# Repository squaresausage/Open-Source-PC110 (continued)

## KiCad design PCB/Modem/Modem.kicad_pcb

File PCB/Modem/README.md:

## Here is the PCB Layout for the Modem Board

Layer Stack-up

| Index | Layer name | Description  |
| ----- | ---------- | ------------ |
| 1     | FC         | Top          |
| 2     | IC1        | Signal       |
| 4     | IP1        | Power        |
| 3     | IP2        | Power        |
| 4     | IC2        | Signal       |
| 4     | BC         | Bottom       |

Here is a render of FC, IC1, IP1, IP2, IC2 and BC:

Here are the 3D renders from the board:

PCB statistics report
=====================
- Date: Friday, March 21, 2025 at 08:35:15 PM
- Project: Modem
- Board name: Modem

Board
-----
- Width: 64.6100 mm
- Height: 58.9100 mm
- Area: 3494.8376 mm²

Pads
----
- Through hole: 23
- SMD: 735
- Connector: 0
- NPTH: 0

Vias
----
- Through vias: 344
- Blind/buried: 0
- Micro vias: 0

Components
----------

|              | Front Side | Back Side | Total |
|--------------|------------|-----------|-------|
|THT:          |          0 |         0 |     0 |
|SMD:          |         75 |       136 |   211 |
|Unspecified:  |          0 |         0 |     0 |
|Total:        |         75 |       136 |   211 |

Drill holes
-----------

| Count | Shape |    X Size |    Y Size | Plated | Via/Pad | Start Layer | Stop Layer |
|-------|-------|-----------|-----------|--------|---------|-------------|------------|
|   344 | Round | 0.3000 mm | 0.3000 mm |    PTH |     Via |          FC |         BC |
|    18 | Round | 1.0000 mm | 1.0000 mm |    PTH |     Pad |          FC |         BC |
|     5 | Round | 1.2000 mm | 1.2000 mm |    PTH |     Pad |          FC |         BC |

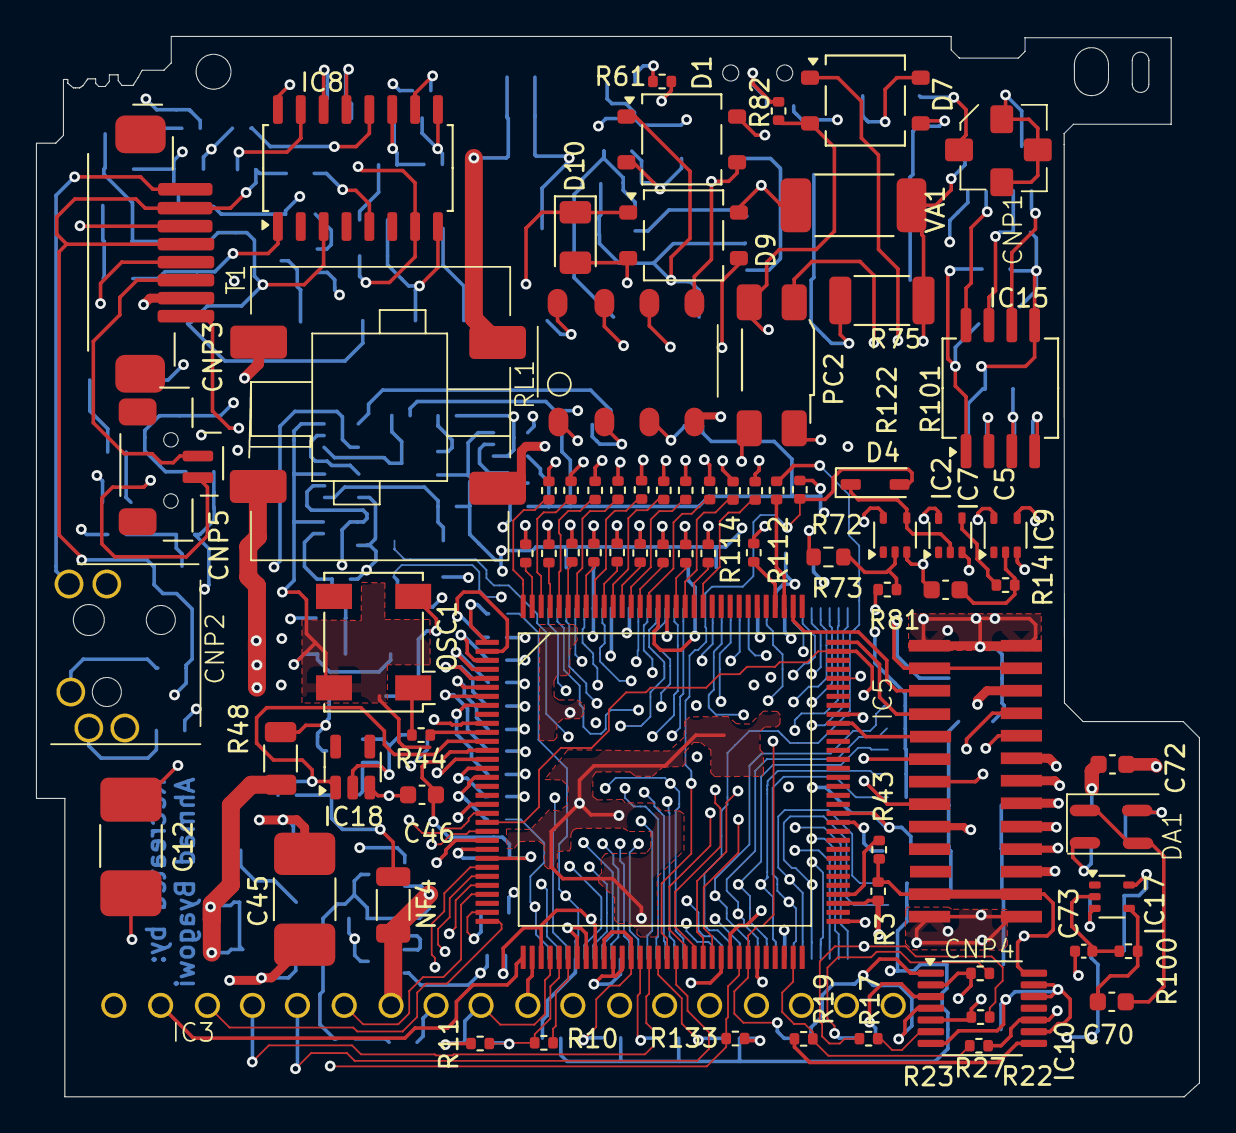
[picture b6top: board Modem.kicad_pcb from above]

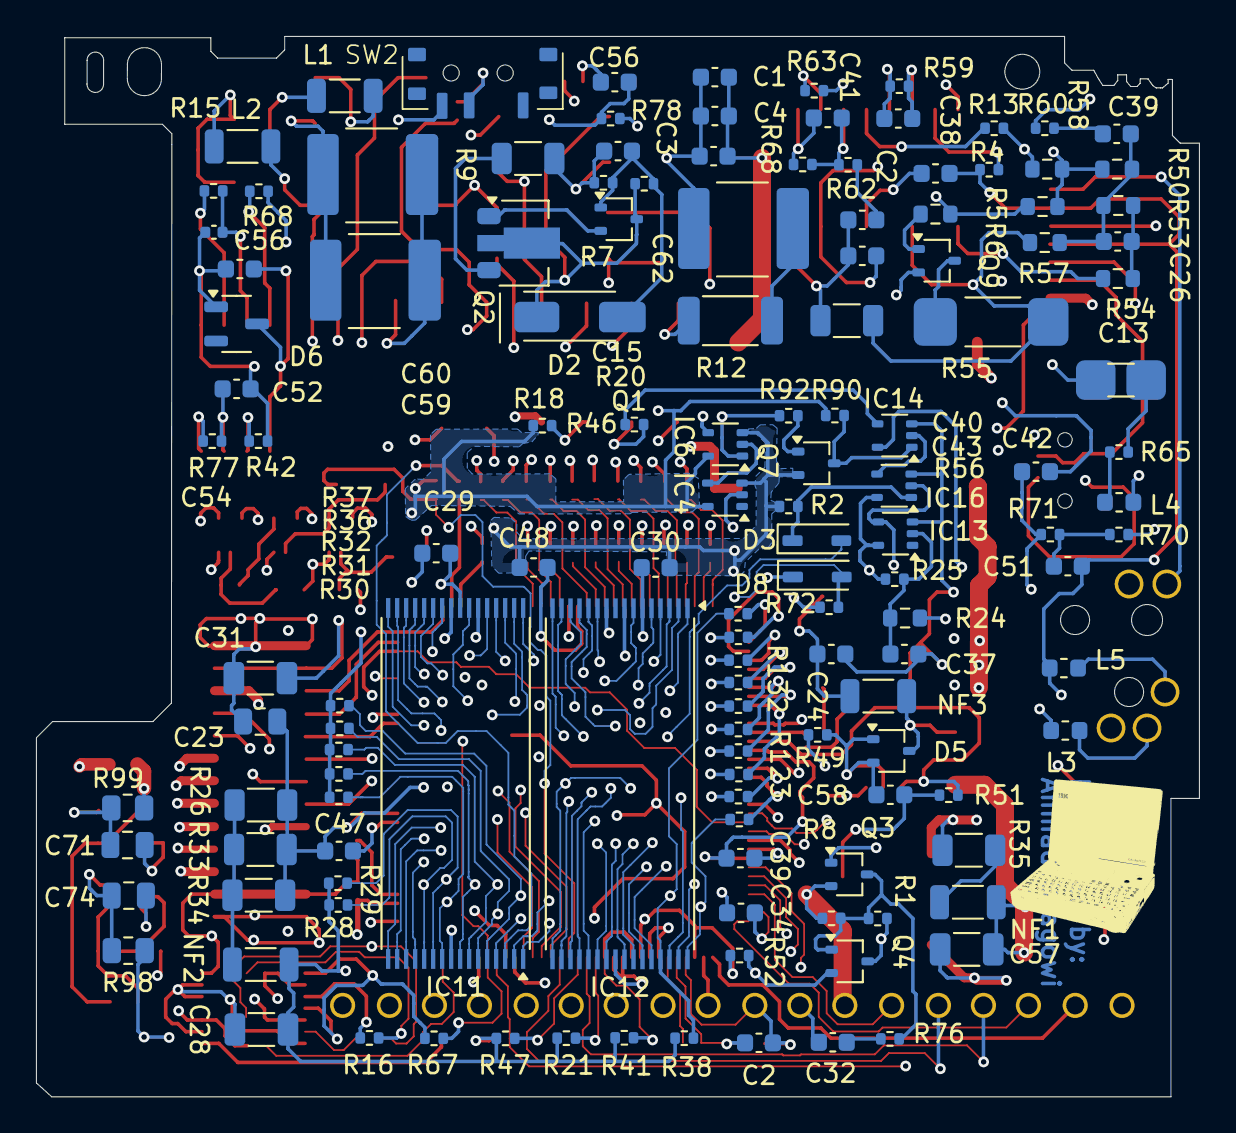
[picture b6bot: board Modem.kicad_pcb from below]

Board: 6 copper layers, 64.6 x 58.9 mm, 211 parts (136 on the bottom side), 205 nets.

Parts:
C1, C4, C52, C54: 330nF; C_0603_1608Metric
C2, C34: 1nF; C_0603_1608Metric
C2#2, C15, C32: 1.2uF; C_0603_1608Metric
C3: 30nF; C_0603_1608Metric
C5: 250nF; C_0603_1608Metric
C12, C45: 47uF 16v; C_1812_4532Metric
C13: 822J; C_1206_3216Metric
C23: 1.2uF; C_0805_2012Metric
C24, C37: 230nF; C_0603_1608Metric
C26: 10nF; C_0603_1608Metric
C28: 8.1uF; C_1206_3216Metric
C29, C30: 1.5uF; C_0603_1608Metric
C31: 230nF; C_1206_3216Metric
C38: 2.2uF; C_0603_1608Metric
C39: 100nF; C_0603_1608Metric
C39#2, C48: 25nF; C_0603_1608Metric
C40: 16nF; C_0603_1608Metric
C41, C43: 1uF; C_0603_1608Metric
C42, C51: 1.2nF; C_0603_1608Metric
C46, C47: 24nF; C_0603_1608Metric
C56: 1.6nF; C_0402_1005Metric
C56#2: 470nF; C_0603_1608Metric
C57: 6.8uF; C_1206_3216Metric
C58: 220nF; C_0603_1608Metric
C59, C60, C62: 280nF; C_2220_5750Metric
C70, C72: 1.8uF; C_0603_1608Metric
C71: 1.3uF; C_0805_2012Metric
C73: 100pF; C_0402_1005Metric
C74: 220nF; C_0805_2012Metric
CNP1: Line_Connector
CNP2: modem_heaset_jack
CNP3: JST_8_headset_connector
CNP4: Modem-Connector
CNP5: JST_2_modem_spkr
D1, D7, D9: TO-269AA
D2: 1N4148; D_SOD-128
D3, D4, D8: 5; D_1206_3216Metric_modem
D5: 3D; SOT-323_SC-70
D6: 30H; SOT-23-3
D10: 152; D_1206_3216Metric
DA1: M1T; DA_Modem
IC2, IC7, IC9, IC13, IC17: EA; SOT-353_SC-70-5
IC3: Line-Module
IC4: E5; SOT-353_SC-70-5
IC5: MN195
IC6: 54; SOT-353_SC-70-5
IC8: TA31033F; SOIC-16_4.55x10.3mm_P1.27mm
IC10: AT32 433; TSSOP-14_4.4x5mm_P0.65mm
IC11: EN29F040A; TSOP-I-32_18.4x8mm_P0.5mm_Reverse
IC12: KM681000BLT-7 (I-Reverse); TSOP-I-32_18.4x8mm_P0.5mm_Reverse
IC14: E4; SOT-353_SC-70-5
IC15: 8206 5877; SOIC-8_5.3x6.2mm_P1.27mm
IC16: E3; SOT-353_SC-70-5
IC18: 3L01; TSOT-23-5
L1, L2: 1.2uH; L_1206_3216Metric
L3, L5: 1.8uH; L_0603_1608Metric
L4: 1.2uH; L_0603_1608Metric
NF1: 300nH; L_1206_3216Metric
NF2, NF4: 4.7nH; L_1206_3216Metric
NF3: 0; L_1206_3216Metric
OSC1: 41.472; Oscillator_SMD_Fordahl_DFAS2-4Pin_7.3x5.1mm
PC2: TLP124; Everlight_ITR8307_Reverse
Q1, Q4: CQ; SOT-323_SC-70
Q2: DA QU; SOT-89-3
Q3: 123; SOT-323_SC-70
Q7: SOT-323_SC-70
Q9: HP; SOT-323_SC-70
R1: 12k; R_0402_1005Metric
R2, R3, R28, R29, R30, R31, R32, R36, R37, R38, R41, R43: 4.7k; R_0402_1005Metric
R4: 330; R_0402_1005Metric
R5: 100; R_0603_1608Metric
R6: 3.3k; R_0603_1608Metric
R7, R26, R33, R34: 10; R_1206_3216Metric
R8: 22k; R_0402_1005Metric
R9, R20, R63, R81: 100k; R_0402_1005Metric
R10, R11, R68: 38k; R_0402_1005Metric
R12, R75: 2.2k; R_2010_5025Metric
R13, R16, R17, R19, R21, R47, R49, R62, R67, R82, R133: 10k; R_0402_1005Metric
R14: 560k; R_0402_1005Metric
R15: 330k; R_0402_1005Metric
R18, R46: 1.5k; R_0402_1005Metric
R22, R23, R27: DNP; R_0402_1005Metric
R24: 200; R_0603_1608Metric
R25: 500k; R_0402_1005Metric
R35: 20; R_1206_3216Metric
R42: 15k; R_0402_1005Metric
R44: 51; R_0402_1005Metric
R48: 3.3; R_1206_3216Metric
R50: 6.2k; R_0603_1608Metric
R51, R72, R72#2, R90, R100: 470k; R_0402_1005Metric
R52, R70, R71: 1k; R_0402_1005Metric
R53: 11k; R_0603_1608Metric
R54: 1.5k; R_0603_1608Metric
R55: 82; R_2010_5025Metric
R56: 15; R_1206_3216Metric
R57: 150; R_0603_1608Metric
R58: 620; R_0603_1608Metric
R59, R60: 2.2k; R_0402_1005Metric
R61: 3.6k; R_0402_1005Metric
R65: 15; R_0402_1005Metric
R68#2: 20k; R_0402_1005Metric
R73: 120; R_0603_1608Metric
R76: 2.4k; R_0402_1005Metric
R77: 270k; R_0402_1005Metric
R78: 5.6k; R_0402_1005Metric
R92: 47k; R_0402_1005Metric
R98, R99: 100; R_0805_2012Metric
R101, R102, R103, R104, R105, R106, R107, R108, R109, R110, R111, R112, R114, R115, R116, R117, R118, R119, R120, R121, R122, R123, R124, R124#2, R125, R126, R127, R129, R130, R131, R132: 100; R_0402_1005Metric
RL1: RL
SW2: SW_modem
T1: IsoTransformer
VA1: R_2512_6332Metric

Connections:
29FA7: IC11.20, IC12.13, R119.1
29F_A0: IC11.13, IC12.20, R111.1
29F_A1: IC11.14, IC12.19, R122.1
29F_A2: IC11.15, IC12.18, R110.1
29F_A3: IC11.16, IC12.17, R121.1
29F_A4: IC11.17, IC12.16, R109.1
29F_A5: IC11.18, IC12.15, R120.1
29F_A6: IC11.19, IC12.14, R108.1
29F_A8: IC11.30, IC12.3, R107.1
29F_A9: IC11.31, IC12.2, R118.1
29F_A10: IC11.2, IC12.31, R106.1
29F_A11: IC11.32, IC12.1, R117.1
29F_A12: IC11.21, IC12.12, R105.1
29F_A13: IC11.29, IC12.4, R116.1
29F_A14: IC11.28, IC12.11, R104.1
29F_A15: IC11.22, IC12.7, R115.1
29F_A16: IC11.23, IC12.10, R103.1
29F_A17: IC11.27, R114.1
29F_A18: IC11.24, R102.1
29F_CE#: IC11.3, R101.1
29F_DQ0: IC11.12, IC12.21, R28.2, R125.1
29F_DQ1: IC11.11, IC12.22, R29.2, R126.1
29F_DQ2: IC11.10, IC12.23, R30.2, R127.1
29F_DQ3: IC11.8, IC12.25, R31.2, R124#2.1
29F_DQ4: IC11.7, IC12.26, R32.2, R129.1
29F_DQ5: IC11.6, IC12.27, R36.2, R130.1
29F_DQ6: IC11.5, IC12.28, R37.2, R131.1
29F_DQ7: IC11.4, IC12.29, R38.2, R132.1
29F_OE#: IC11.1, IC12.32, R123.1
29F_WE#: IC11.26, IC12.5, R124.1
C32_1: C32.1, IC3.8
C32_2: C32.2, R76.1
C39_1: C39.1, R60.2
C40_2: C40.2, R62.2
C51_1: C51.1, R70.1, R71.2
C52_2: C52.2, C54.1, C56.1, D6.1, D7.2, IC15.5, PC2.3, R42.2, R82.1
C70_1: C70.1, IC17.4, R100.1
C70_2: C70.2, DA1.1, DA1.4
C72_1: C72.1, IC3.12, R99.2
C74_1: C74.1, IC17.5, R98.1
CNP2_2: CNP2.2, CNP3.3
CNP2_3: CNP2.3, L4.2
CNP3_1: CNP2.4, CNP3.1
CNP3_5: CNP3.5, R78.2
CNP5_1: CNP5.1, SW2.3
CNP5_2: CNP3.6, CNP5.2
D1_1: D1.1, D2.1, Q1.3, Q2.2, R20.1
D1_2: C15.1, D1.2, R7.2, R9.1
D2_2: C15.2, D2.2, Q1.1, R9.2, R20.2
D4_1: D4.1, IC2.4, IC7.2
D7_1: C54.2, D6.3, D7.1, IC15.1
D7_3: C59.1, C60.1, D7.3
DA1_2: C71.1, DA1.2, R99.1
FDC_CTS1#: CNP4.8, IC10.5, R23.2
FDC_DCD1_PC110: CNP4.4, IC5.65
FDC_DIR1#_PC110: CNP4.6, IC5.54
FDC_DSR1_PC110: CNP4.7, IC5.51
FDC_RI1_PC110: CNP4.5, IC10.2, R22.2
FDC_RTS1#_PC110: CNP4.9, IC5.53
FDC_RXD1_PC110: CNP4.10, IC5.52
FDC_TXD1_PC110: CNP4.11, IC9.4
GND: C5.1, C23.1, C24.2, C28.1, C29.1, C30.2, C31.1, C37.2, C39#2.2, C46.1, C47.2, C48.1, C58.2, CNP3.8, CNP4.1, CNP4.13, CNP4.14, CNP4.26, IC2.3, IC4.3, IC5.10, IC5.14, IC5.19, IC5.24, IC5.43, IC5.44, IC5.76, IC5.112, IC6.3, IC7.3, IC9.3, IC10.1, IC10.4, IC10.7, IC10.9, IC10.12, IC10.13, IC11.9, IC12.24, IC13.3, IC14.3, IC16.3, IC18.3, NF4.2, OSC1.4, Q7.2, R2.1, R51.1, R67.1, R81.1
IC3_15: IC3.15, T1.3
IC6_2: IC4.4, IC6.2
IC7_4: IC7.4, R14.1
IC8_3: IC8.3, R55.2, R56.1, R57.1
IC8_5: C2#2.1, IC8.5
IC8_7: C43.2, IC8.7, R63.2
IC8_9: C41.1, IC8.9, R68.1
IC8_10: C42.2, IC8.10, R63.1
IC8_11: C41.2, IC8.11, R62.1, R68.2
IC8_12: IC8.12, R13.1
IC8_13: C38.1, IC8.13, R59.1, R60.1
IC8_14: C38.2, IC8.14, R59.2
IC8_15: C13.1, IC8.15, R4.2
IC8_16: C12.2, IC8.16, R13.2, R58.1, R70.2
IC9_2: C5.2, IC9.2, R14.2
IC10_6: IC10.6, R17.1
IC10_8: IC10.8, R19.2
IC12_3: IC12.30, R112.1
IC13_2: C37.1, IC13.2, R24.1, R25.2
IC13_4: D8.1, IC13.4, IC16.2
IC14_1: IC14.1, Q7.3, R90.2
IC14_4: IC14.4, R46.1
IC15_2: IC15.2, R42.1
IC15_3: C52.1, IC15.3, R77.2
IC15_4: IC15.4, R77.1
IC15_6: IC15.6, R15.1
IC15_7: C56.2, IC15.7, R15.2
IC15_8: C56#2.2, IC15.8, R68#2.1, R78.1
IC16_1: D3.1, IC16.1, R2.2
IC16_4: IC14.2, IC16.4
IC17_2: C73.2, IC17.2, R100.2
IC18_2: C58.1, D5.1, D5.2, IC18.2, R49.2
IREF2: C34.2, IC5.31
L1_1: D1.4, D7.4, D9.4, L1.2, T1.1, VA1.1
L1_2: L2.2, R12.1, R75.2, RL1.6, RL1.8, VA1.2
L3_1: C42.1, L3.1, R71.1
L3_2: CNP2.1, L3.2
L4_1: L4.1, R65.1
L5_2: CNP2.5, L5.2
MN192_S11_BUF: CNP4.22, Q4.2, R52.2
MN195_A0: IC5.128, R111.2
MN195_A1: IC5.127, R122.2
MN195_A2: IC5.126, R110.2
MN195_A3: IC5.125, R121.2
MN195_A4: IC5.124, R109.2
MN195_A5: IC5.123, R120.2
MN195_A6: IC5.122, R108.2
MN195_A7: IC5.121, R119.2
MN195_A8: IC5.120, R107.2
MN195_A9: IC5.119, R118.2
MN195_A10: IC5.118, R106.2
MN195_A11: IC5.117, R117.2
MN195_A12: IC5.116, R105.2
MN195_A13: IC5.115, R116.2
MN195_A14: IC5.114, R104.2
MN195_A15: IC5.111, R115.2
MN195_A16: IC5.110, R103.2
MN195_A17: IC5.109, R114.2
MN195_A18: IC5.108, R102.2
MN195_ADCK#: CNP4.21, IC5.21, IC5.95
MN195_AGCIN: IC3.18, IC5.28
MN195_AGCOUT: IC3.17, IC5.27
MN195_CX: IC5.11, R44.1
MN195_DVDD1: C23.2, C39#2.1, C46.2, C47.1, C48.2, IC5.13, IC5.25, IC5.77, IC5.113, R26.1, R33.1, R34.1
MN195_HDRES#: IC5.12, IC18.1, R51.2
MN195_HPOUT: IC3.6, IC5.29
MN195_HVDD: IC3.2, IC5.33
MN195_IREF0: IC5.38, R10.1
MN195_IREF1: C2.1, IC5.37, R10.2, R11.1
MN195_IRQ1#: CNP4.20, IC5.67, R3.1
MN195_IRQ2#: IC5.68, R43.2
MN195_MD0: IC5.8, R125.2
MN195_MD1: IC5.7, R126.2
MN195_MD2: IC5.6, R127.2
MN195_MD3: IC5.5, R124#2.2
MN195_MD4: IC5.4, R129.2
MN195_MD5: IC5.3, R130.2
MN195_MD6: IC5.2, R131.2
MN195_MD7: IC5.1, R132.2
MN195_MOD1,3: IC5.42, IC5.45, R41.2
MN195_MTA1: IC3.11, IC5.92
MN195_PLSD: IC3.1, IC5.23
MN195_RD#: IC5.16, R123.2
MN195_RXL: IC3.3, IC5.32
MN195_S0: IC5.46, IC6.1, R21.2, R92.1
MN195_S1: IC3.4, IC5.47
MN195_S2: IC4.2, IC5.48, R47.2
MN195_S3: D4.2, IC5.49, R72.2
MN195_S4: IC3.5, IC5.50
MN195_S9: IC5.55, R16.2, R22.1
MN195_S10: IC5.56, R17.2, R23.1
MN195_S11: IC5.57, Q3.1, R133.2
MN195_S12: D3.2, IC5.58, R67.2
MN195_S13: D8.2, IC5.59, R72#2.2
MN195_SHIN: IC3.16, IC5.26
MN195_TXLPIN: C2.2, IC3.9, IC5.36, R11.2
MN195_TXOUT: IC3.10, IC5.34
MN195_U1RD#: IC5.63, R19.1, R27.2
MN195_U1RD#_R: CNP4.3, IC10.10, R27.1
MN195_UC0#: IC5.99, R101.2
MN195_UC1: IC5.100, R112.2
MN195_VPCK#: CNP4.18, IC5.87
MN195_VPDA#: CNP4.19, IC5.88
MN195_VREEH: C45.2, IC5.39, IC5.40, R35.2
MN195_VSDA#: CNP4.17, IC5.96
MN195_VSEN#: CNP4.16, IC5.98
MN195_WR#: IC5.15, R124.2
NF1_1: NF1.1, R35.1
NF2_1: NF2.1, R26.2, R33.2, R34.2
OSC1_1: OSC1.1, R44.2
OSC1_2: C24.1, NF3.1, OSC1.2
PC2_1: PC2.1, R68#2.2
PNET1: C57.2, IC3.13, NF1.2, Q4.3, R1.2, R48.1, R98.2
PNET4: C45.1, C57.1, C71.2, C72.2, C73.1, C74.2, DA1.3, IC3.7, IC3.14, IC5.35, IC5.41, IC17.3, NF4.1, Q3.2, R8.1, R52.1, T1.2
Pluto_Enabled_PNET5: C31.2, CNP4.12, CNP4.15, IC2.5, IC7.5, IC9.5, IC13.5, IC14.5, IC16.5, PC2.2, R25.1, RL1.1
Q2_1: Q1.2, Q2.1, Q2.3, R7.1
Q3_3: Q3.3, Q4.1, R1.1, R8.2, R76.2
Q7_1: Q7.1, R92.2
Q9_1: Q9.1, R6.1
R6_2: R5.1, R6.2
R12_2: C62.2, R12.2
R16_1: IC10.3, R16.1
R24_2: CNP3.7, R24.2
R54_1: D9.1, D10.1, IC8.1, Q9.2, R5.2, R50.1, R54.1, R58.2
R54_2: C26.2, R53.2, R54.2
R55_1: Q9.3, R55.1
R56_2: C2#2.2, C12.1, C40.1, C43.1, C51.2, CNP3.2, CNP3.4, D9.2, D10.2, IC8.8, L5.1, R4.1, R56.2
R57_2: C26.1, C39.2, R50.2, R53.1, R57.2
R61_2: C56#2.1, R61.2
R65_2: C13.2, R65.2
R73_2: IC2.2, R73.2, R81.2
R75_1: C59.2, C60.2, R75.1
R82_2: R61.1, R82.2, SW2.2
RL1_2: R46.2, RL1.2
RL1_3: R18.2, RL1.3
RL1_4: IC6.4, RL1.4
RL1_5: C1.1, C3.1, C4.1, C62.1, D1.3, RL1.5
RL1_7: D9.3, RL1.7
T1_4: C1.2, C3.2, C4.2, T1.4
TEL_GND: CNP1.2, CNP1.3, CNP1.4, L2.1
TEL_Line: CNP1.1, L1.1
TLP124_4: PC2.4, R73.1
VCC_PC110: C28.2, C29.2, C30.1, CNP4.2, CNP4.25, D5.3, IC4.5, IC6.5, IC10.14, IC11.25, IC12.6, IC12.8, NF2.2, NF3.2, R3.2, R18.1, R21.1, R28.1, R29.1, R30.1, R31.1, R32.1, R36.1, R37.1, R38.1, R41.1, R43.1, R47.1, R48.2, R49.1, R72.1, R72#2.1, R90.1, R133.1

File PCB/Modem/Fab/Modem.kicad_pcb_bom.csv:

Designator,Quantity,Value,Footprint,Package,MPN,DNP,Mount_Type
"C1, C4, C52, C54",4,330nF,C_0603_1608Metric,,,,smt
"C12, C45",2,47uF 16v,C_1812_4532Metric,,,,smt
C13,1,822J,C_1206_3216Metric,,,,smt
"C15, C2, C32",3,1.2uF,C_0603_1608Metric,,,,smt
"C2, C34",2,1nF,C_0603_1608Metric,,,,smt
C23,1,1.2uF,C_0805_2012Metric,,,,smt
"C24, C37",2,230nF,C_0603_1608Metric,,,,smt
C26,1,10nF,C_0603_1608Metric,,,,smt
C28,1,8.1uF,C_1206_3216Metric,,,,smt
"C29, C30",2,1.5uF,C_0603_1608Metric,,,,smt
C3,1,30nF,C_0603_1608Metric,,,,smt
C31,1,230nF,C_1206_3216Metric,,,,smt
C38,1,2.2uF,C_0603_1608Metric,,,,smt
C39,1,100nF,C_0603_1608Metric,,,,smt
"C39, C48",2,25nF,C_0603_1608Metric,,,,smt
C40,1,16nF,C_0603_1608Metric,,,,smt
"C41, C43",2,1uF,C_0603_1608Metric,,,,smt
"C42, C51",2,1.2nF,C_0603_1608Metric,,,,smt
"C46, C47",2,24nF,C_0603_1608Metric,,,,smt
C5,1,250nF,C_0603_1608Metric,,,,smt
C56,1,1.6nF,C_0402_1005Metric,,,,smt
C56,1,470nF,C_0603_1608Metric,,,,smt
C57,1,6.8uF,C_1206_3216Metric,,,,smt
C58,1,220nF,C_0603_1608Metric,,,,smt
"C59, C60, C62",3,280nF,C_2220_5750Metric,,,,smt
"C70, C72",2,1.8uF,C_0603_1608Metric,,,,smt
C71,1,1.3uF,C_0805_2012Metric,,,,smt
C73,1,100pF,C_0402_1005Metric,,,,smt
C74,1,220nF,C_0805_2012Metric,,,,smt
CNP1,1,Line_Connector,Line_Connector,,,,smt
CNP2,1,modem_heaset_jack,modem_heaset_jack,,,,smt
CNP3,1,JST_8_headset_connector,JST_8_headset_connector,,,,smt
CNP4,1,Modem-Connector,Modem-Connector,,,,smt
CNP5,1,JST_2_modem_spkr,JST_2_modem_spkr,,,,smt
"D1, D7, D9",3,TO-269AA,TO-269AA,,,,smt
D10,1,152,D_1206_3216Metric,,,,smt
D2,1,1N4148,D_SOD-128,,,,smt
"D3, D4, D8",3,5,D_1206_3216Metric_modem,,,,smt
D5,1,3D,SOT-323_SC-70,,,,smt
D6,1,30H,SOT-23-3,,,,smt
DA1,1,M1T,DA_Modem,,,,smt
IC10,1,AT32 433,TSSOP-14_4.4x5mm_P0.65mm,,,,smt
IC11,1,EN29F040A,TSOP-I-32_18.4x8mm_P0.5mm_Reverse,,,,smt
IC12,1,KM681000BLT-7 (I-Reverse),TSOP-I-32_18.4x8mm_P0.5mm_Reverse,,,,smt
"IC13, IC17, IC2, IC7, IC9",5,EA,SOT-353_SC-70-5,,,,smt
IC14,1,E4,SOT-353_SC-70-5,,,,smt
IC15,1,8206 5877,SOIC-8_5.3x6.2mm_P1.27mm,,,,smt
IC16,1,E3,SOT-353_SC-70-5,,,,smt
IC18,1,3L01,TSOT-23-5,,,,smt
IC3,1,Line-Module,Line-Module,,,,smt
IC4,1,E5,SOT-353_SC-70-5,,,,smt
IC5,1,MN195,MN195,,,,smt
IC6,1,54,SOT-353_SC-70-5,,,,smt
IC8,1,TA31033F,SOIC-16_4.55x10.3mm_P1.27mm,,,,smt
"L1, L2",2,1.2uH,L_1206_3216Metric,,,,smt
"L3, L5",2,1.8uH,L_0603_1608Metric,,,,smt
L4,1,1.2uH,L_0603_1608Metric,,,,smt
NF1,1,300nH,L_1206_3216Metric,,,,smt
"NF2, NF4",2,4.7nH,L_1206_3216Metric,,,,smt
NF3,1,0,L_1206_3216Metric,,,,smt
OSC1,1,41.472,Oscillator_SMD_Fordahl_DFAS2-4Pin_7.3x5.1mm,,,,smt
PC2,1,TLP124,Everlight_ITR8307_Reverse,,,,smt
"Q1, Q4",2,CQ,SOT-323_SC-70,,,,smt
Q2,1,DA QU,SOT-89-3,,,,smt
Q3,1,123,SOT-323_SC-70,,,,smt
Q7,1,SOT-323_SC-70,SOT-323_SC-70,,,,smt
Q9,1,HP,SOT-323_SC-70,,,,smt
R1,1,12k,R_0402_1005Metric,,,,smt
"R10, R11, R68",3,38k,R_0402_1005Metric,,,,smt
"R100, R51, R72, R72, R90",5,470k,R_0402_1005Metric,,,,smt
"R101, R102, R103, R104, R105, R106, R107, R108, R109, R110, R111, R112, R114, R115, R116, R117, R118, R119, R120, R121, R122, R123, R124, R124, R125, R126, R127, R129, R130, R131, R132",31,100,R_0402_1005Metric,,,,smt
"R12, R75",2,2.2k,R_2010_5025Metric,,,,smt
"R13, R133, R16, R17, R19, R21, R47, R49, R62, R67, R82",11,10k,R_0402_1005Metric,,,,smt
R14,1,560k,R_0402_1005Metric,,,,smt
R15,1,330k,R_0402_1005Metric,,,,smt
"R18, R46",2,1.5k,R_0402_1005Metric,,,,smt
"R2, R28, R29, R3, R30, R31, R32, R36, R37, R38, R41, R43",12,4.7k,R_0402_1005Metric,,,,smt
"R20, R63, R81, R9",4,100k,R_0402_1005Metric,,,,smt
R22,1,DNP,R_0402_1005Metric,,,Yes,smt
R23,1,DNP,R_0402_1005Metric,,,Yes,smt
R24,1,200,R_0603_1608Metric,,,,smt
R25,1,500k,R_0402_1005Metric,,,,smt
"R26, R33, R34, R7",4,10,R_1206_3216Metric,,,,smt
R27,1,DNP,R_0402_1005Metric,,,Yes,smt
R35,1,20,R_1206_3216Metric,,,,smt
R4,1,330,R_0402_1005Metric,,,,smt
R42,1,15k,R_0402_1005Metric,,,,smt
R44,1,51,R_0402_1005Metric,,,,smt
R48,1,3.3,R_1206_3216Metric,,,,smt
R5,1,100,R_0603_1608Metric,,,,smt
R50,1,6.2k,R_0603_1608Metric,,,,smt
"R52, R70, R71",3,1k,R_0402_1005Metric,,,,smt
R53,1,11k,R_0603_1608Metric,,,,smt
R54,1,1.5k,R_0603_1608Metric,,,,smt
R55,1,82,R_2010_5025Metric,,,,smt
R56,1,15,R_1206_3216Metric,,,,smt
R57,1,150,R_0603_1608Metric,,,,smt
R58,1,620,R_0603_1608Metric,,,,smt
"R59, R60",2,2.2k,R_0402_1005Metric,,,,smt
R6,1,3.3k,R_0603_1608Metric,,,,smt
R61,1,3.6k,R_0402_1005Metric,,,,smt
R65,1,15,R_0402_1005Metric,,,,smt
R68,1,20k,R_0402_1005Metric,,,,smt
R73,1,120,R_0603_1608Metric,,,,smt
R76,1,2.4k,R_0402_1005Metric,,,,smt
R77,1,270k,R_0402_1005Metric,,,,smt
R78,1,5.6k,R_0402_1005Metric,,,,smt
R8,1,22k,R_0402_1005Metric,,,,smt
R92,1,47k,R_0402_1005Metric,,,,smt
"R98, R99",2,100,R_0805_2012Metric,,,,smt
RL1,1,RL,RL,,,,smt
SW2,1,SW_modem,SW_modem,,,,smt
T1,1,IsoTransformer,IsoTransformer,,,,smt
VA1,1,R_2512_6332Metric,R_2512_6332Metric,,,,smt
